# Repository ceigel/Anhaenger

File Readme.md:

## Anhaenger Lighting

This is an Arduino project to provide lighting for a Bike trailer for children. 
The controller supports 3 light strips: 1 under the body with a blue side-to-side pattern and 2 light strips innen on each side of the sits. There are 2 buttons which can control the inside strips, with 3 different patterns, one for iddle, the other 2 changeable via double-click on the buttons. There is a speed sensors which controls the light pattern of the under-body light strip, when decelerating it changes to all-red. When no input from the buttons or from the speed sensor, the controller sleeps. It can be brought back via button presses.

The project contains also kicad files for a PCB. The PCB has support for one extra light strip and a light sensor.

The project also contains Fusion 360 and step files for 3D printing the box containing the PCB.

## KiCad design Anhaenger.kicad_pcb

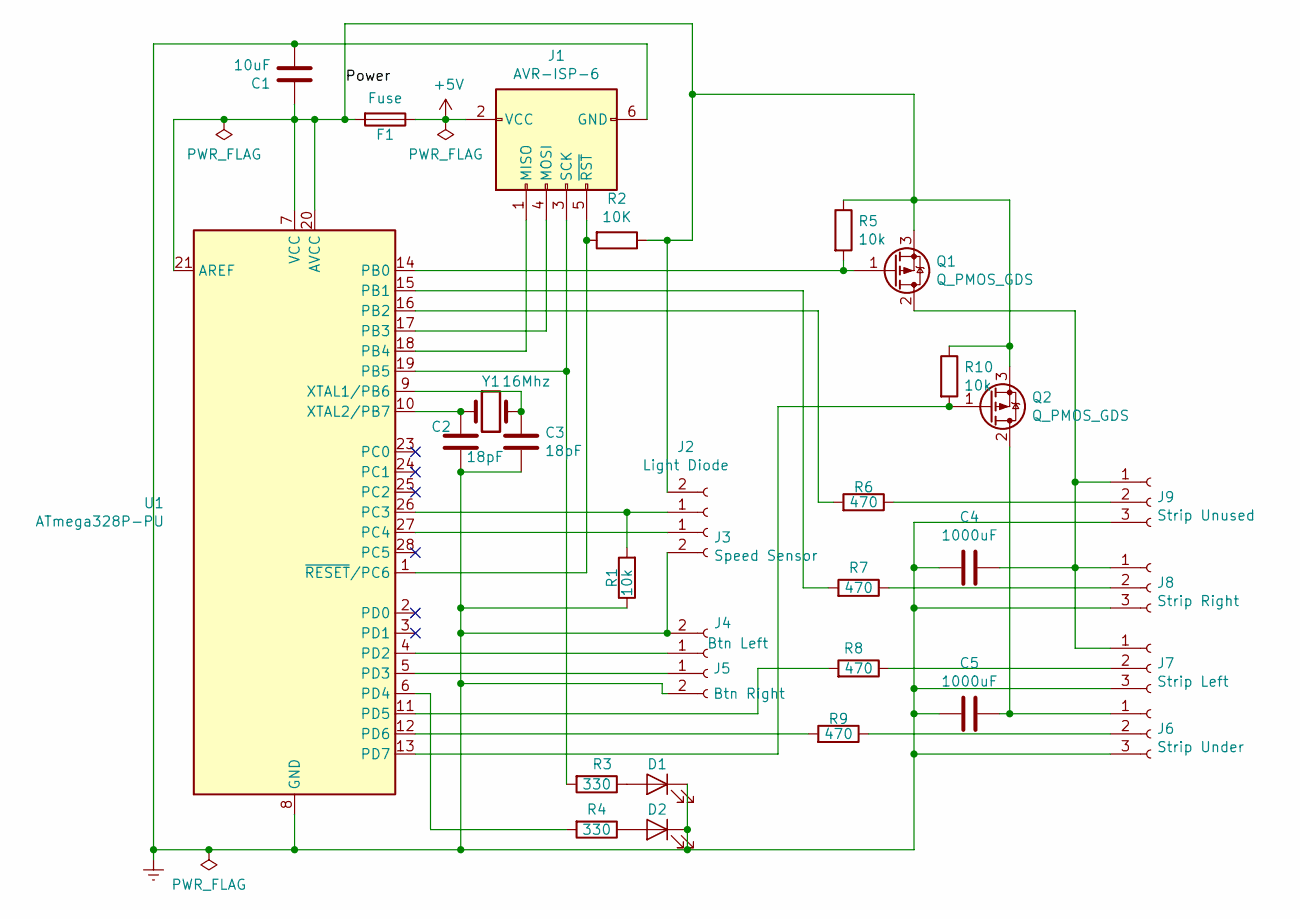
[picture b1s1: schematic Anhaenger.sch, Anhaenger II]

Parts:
C1: 10uF; C_Radial_D5.0mm_H7.0mm_P2.00mm
C2, C3: 18pF; C_Disc_D3.0mm_W1.6mm_P2.50mm
C4, C5: 1000uF; C_Radial_D8.0mm_H11.5mm_P3.50mm
D1, D2: LED; LED_D5.0mm
F1: Fuse; Fuse_Bourns_MF-RG300
J1: AVR-ISP-6; IDC-Header_2x03_P2.54mm_Vertical
J2: Light Diode; PhoenixContact_MCV_1,5_2-G-3.81_1x02_P3.81mm_Vertical
J3: Speed Sensor; PhoenixContact_MCV_1,5_2-G-3.81_1x02_P3.81mm_Vertical
J4: Btn Left; PhoenixContact_MCV_1,5_2-G-3.81_1x02_P3.81mm_Vertical
J5: Btn Right; PhoenixContact_MCV_1,5_2-G-3.81_1x02_P3.81mm_Vertical
J6: Strip Under; PhoenixContact_MCV_1,5_3-G-3.81_1x03_P3.81mm_Vertical
J7: Strip Left; PhoenixContact_MCV_1,5_3-G-3.81_1x03_P3.81mm_Vertical
J8: Strip Right; PhoenixContact_MCV_1,5_3-G-3.81_1x03_P3.81mm_Vertical
J9: Strip Unused; PhoenixContact_MCV_1,5_3-G-3.81_1x03_P3.81mm_Vertical
Q1, Q2: Q_PMOS_GDS; TO-220-3_Vertical
R1, R5, R10: 10k; R_Axial_DIN0207_L6.3mm_D2.5mm_P7.62mm_Horizontal
R2: 10K; R_Axial_DIN0207_L6.3mm_D2.5mm_P7.62mm_Horizontal
R3, R4: 330; R_Axial_DIN0207_L6.3mm_D2.5mm_P7.62mm_Horizontal
R6, R7, R8, R9: 470; R_Axial_DIN0207_L6.3mm_D2.5mm_P7.62mm_Horizontal
U1: ATmega328P-PU; DIP-28_W7.62mm
Y1: 16Mhz; Crystal_HC49-4H_Vertical

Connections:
+5V: F1.1, J1.2 (VCC)
/Power: C1.1, F1.2, J2.2, Q1.3 (S), Q2.3 (S), R2.1, R5.1, R10.1, U1.7 (VCC), U1.20 (AVCC), U1.21 (AREF)
Earth: C1.2, C2.1, C3.1, C4.2, C5.2, D1.1 (K), D2.1 (K), J1.6 (GND), J3.2, J4.2, J5.2, J6.3, J7.3, J8.3, J9.3, R1.1, U1.8 (GND), U1.22 (GND)
unnamed: C2.2, U1.10 (XTAL2/PB7), Y1.1
unnamed: C3.2, U1.9 (XTAL1/PB6), Y1.2
unnamed: C4.1, J7.1, J8.1, J9.1, Q1.2 (D)
unnamed: C5.1, J6.1, Q2.2 (D)
unnamed: D1.2 (A), R3.1
unnamed: D2.2 (A), R4.1
unnamed: J1.1 (MISO), U1.18 (PB4)
unnamed: J1.3 (SCK), R3.2, U1.19 (PB5)
unnamed: J1.4 (MOSI), U1.17 (PB3)
unnamed: J1.5 (~RST), R2.2, U1.1 (~RESET~/PC6)
unnamed: J2.1, R1.2, U1.26 (PC3)
unnamed: J3.1, U1.27 (PC4)
unnamed: J4.1, U1.4 (PD2)
unnamed: J5.1, U1.5 (PD3)
unnamed: J6.2, R9.1
unnamed: J7.2, R8.1
unnamed: J8.2, R7.1
unnamed: J9.2, R6.1
unnamed: Q1.1 (G), R5.2, U1.14 (PB0)
unnamed: Q2.1 (G), R10.2, U1.13 (PD7)
unnamed: R4.2, U1.6 (PD4)
unnamed: R6.2, U1.16 (PB2)
unnamed: R7.2, U1.15 (PB1)
unnamed: R8.2, U1.11 (PD5)
unnamed: R9.2, U1.12 (PD6)

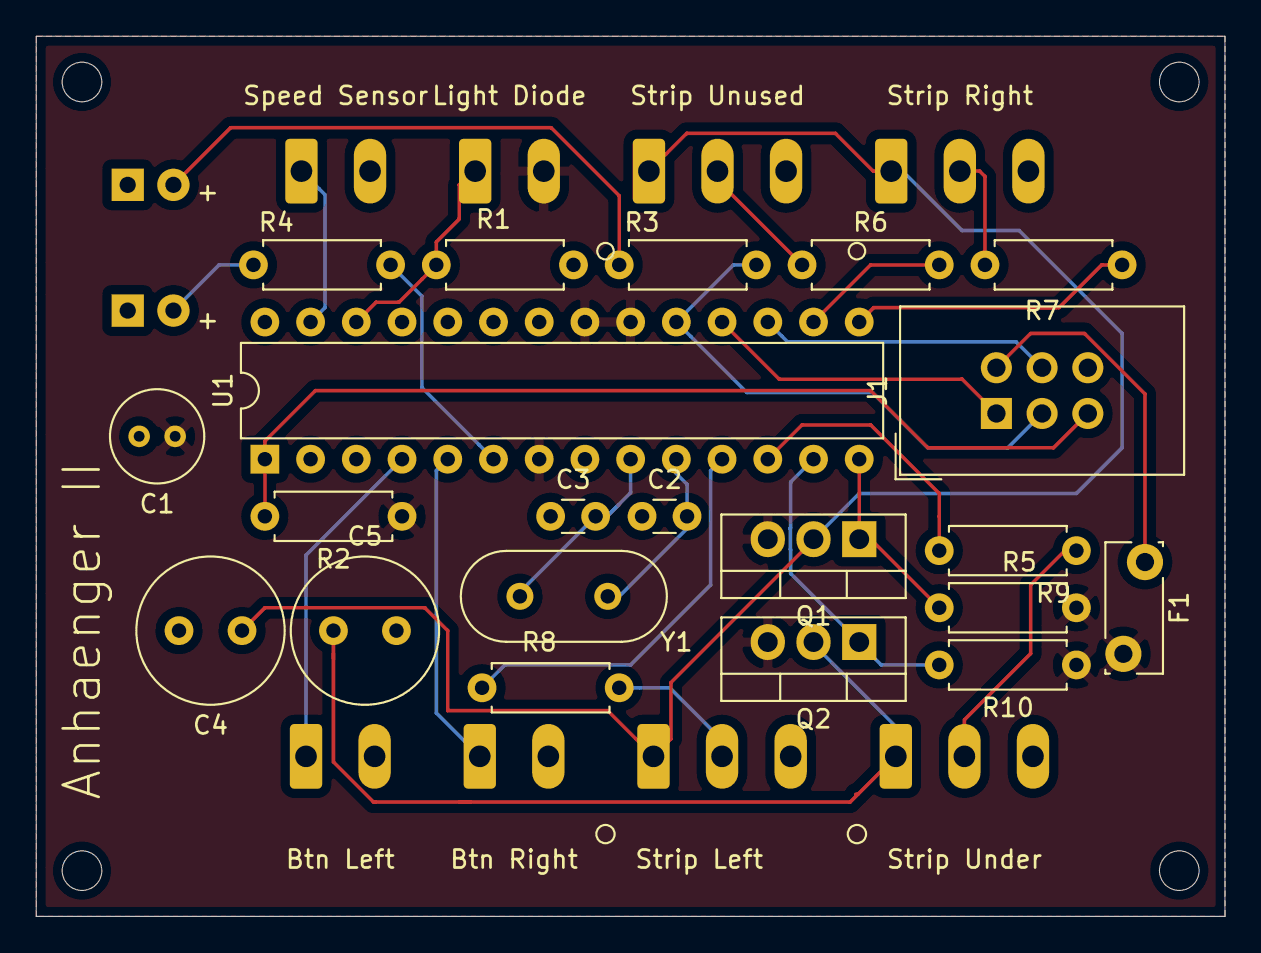
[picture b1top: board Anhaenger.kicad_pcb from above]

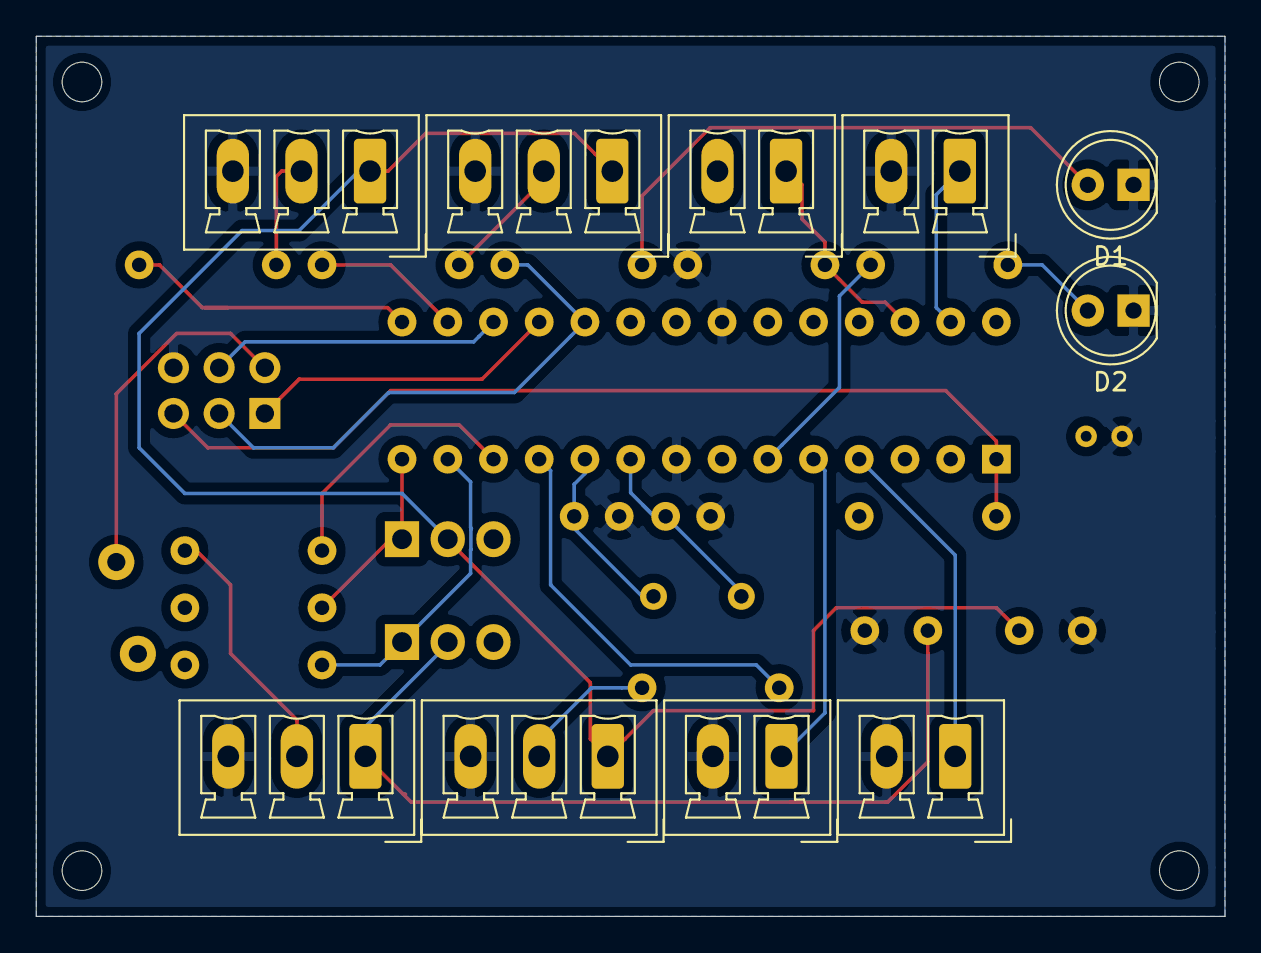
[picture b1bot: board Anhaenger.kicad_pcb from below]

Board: 2 copper layers, 66.0 x 48.9 mm, 31 parts (10 on the bottom side), 28 nets.

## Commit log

2018-06-06 First version
2018-06-08 Increase luminosity of strip
2019-04-23 Add ButtonSensingTask
2019-09-22 Button pressing computation, trial
2019-09-22 Button, lights, sleep work
2019-10-03 Buttons block each other
2019-10-05 Improve sleep and button pressed
2020-03-10 Small improvements
2020-03-10 Add kicad, step and Fusion360 files
2021-01-22 Update kicad file, add support for test led strip
2021-01-22 Add license file
